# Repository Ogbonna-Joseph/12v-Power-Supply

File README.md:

# 12v-Power-Supply
This is a 12 volts power supply circuit.
We used the bridge diode for the rectification section.
<br>
### COMPONENTS USED
- Bridge rectifier diode
- 1000uf Capacitor x2
- Resistor 1k
- LED
- Voltage Regulator LM7812
- DC Jack
- Switch
- Connector

<h3>Power Supply Design.<h3>

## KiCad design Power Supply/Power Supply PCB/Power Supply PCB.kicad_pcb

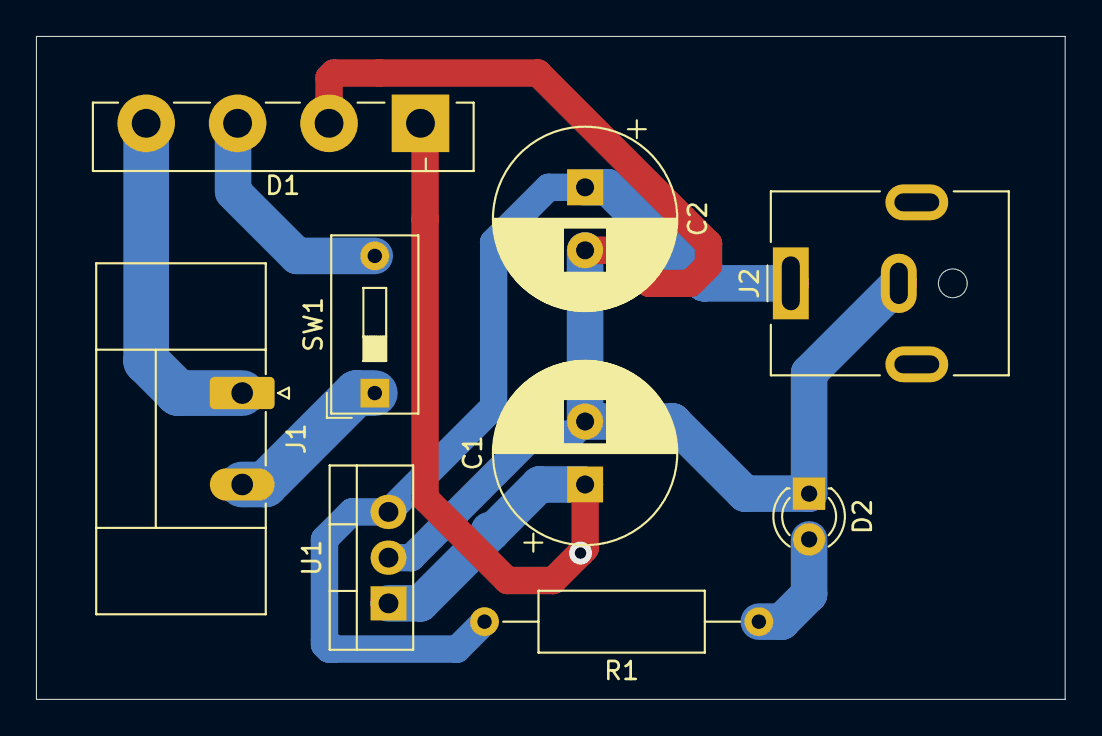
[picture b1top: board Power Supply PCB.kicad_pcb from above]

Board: 2 copper layers, 57.2 x 36.8 mm, 9 parts (0 on the bottom side), 7 nets.

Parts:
C1, C2: 1000uf/25v; CP_Radial_D10.0mm_P3.50mm
D1: Diode RF; Diode_Bridge_Vishay_GBL
D2: LED; LED_D3.0mm
J1: Conn_01x02_Female; PhoenixContact_MC_1,5_2-GF-5.08_1x02_P5.08mm_Horizontal_Thr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
J2: DC Output; BarrelJack_CUI_PJ-063AH_Horizontal
R1: 330R; R_Axial_DIN0309_L9.0mm_D3.2mm_P15.24mm_Horizontal
SW1: Switch; SW_DIP_SPSTx01_Slide_9.78x4.72mm_W7.62mm_P2.54mm
U1: 12v Regulator; TO-220-3_Vertical

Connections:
GND: C1.2, C2.2, D1.2, D2.1, J2.1, J2.2, U1.2
unnamed: C1.1, D1.1, U1.1
unnamed: C2.1, R1.2, U1.3
unnamed: D1.3, SW1.2
unnamed: D1.4, J1.1
unnamed: D2.2, R1.1
unnamed: J1.2, SW1.1

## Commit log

2021-10-24 Create power
